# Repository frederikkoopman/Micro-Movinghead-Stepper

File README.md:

# Micro-Movinghead-Stepper
Micro Movinghead project stepper version

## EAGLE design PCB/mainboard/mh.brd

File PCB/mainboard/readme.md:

All Eagle files are here if your only interested in building not designing the zip file has all the files you need to order a PCB at your favorite PCB maker.

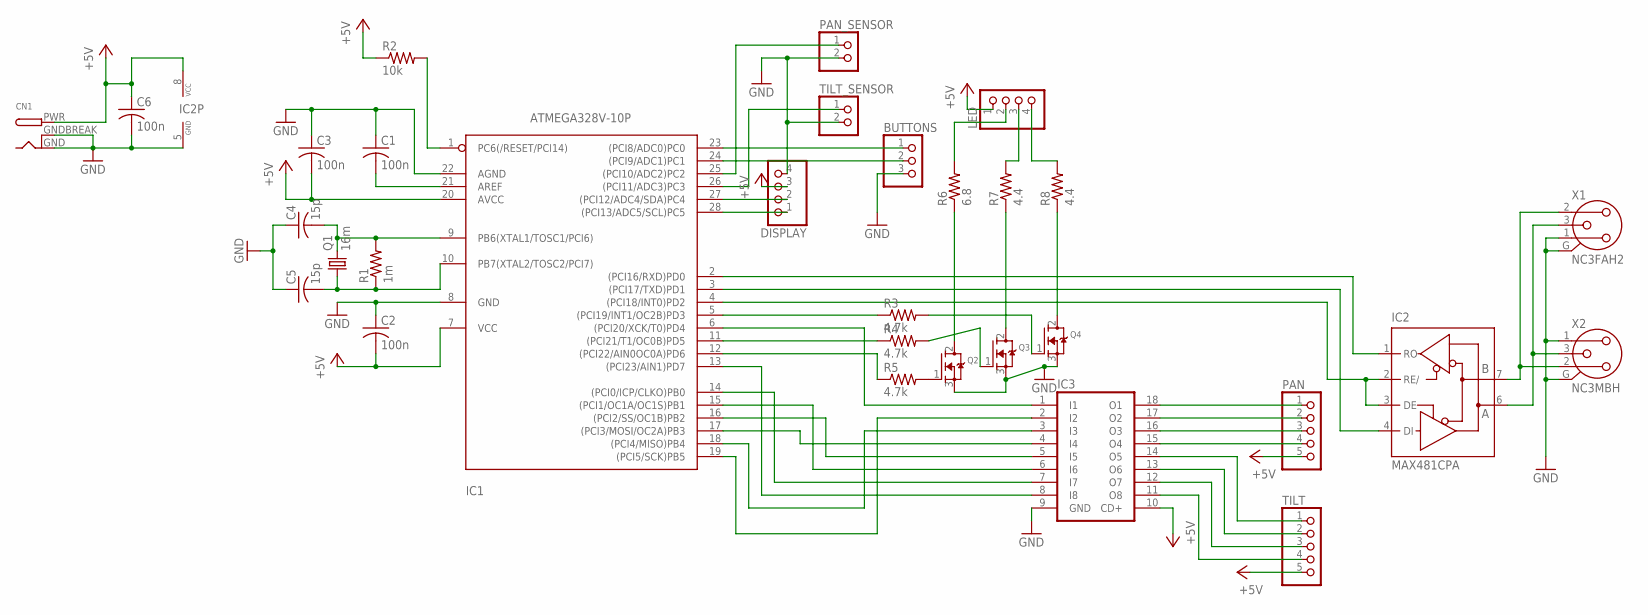
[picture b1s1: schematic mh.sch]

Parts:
BUTTONS: PINHD-1X3; 1X03
C1, C2, C3, C6: 100n; C025-024X044
C4, C5: 15p; C050-024X044
CN1: DCBARRELPTH; DCJACK_2MM_PTH
DISPLAY: PINHD-1X4; 1X04
IC1: ATMEGA328V-10P; DIL28-3
IC2: MAX481CPA; DIL08
IC3: ULN2803A; DIL18
LED: PINHD-1X4; 1X04
PAN: PINHD-1X5; 1X05
PAN_SENSOR: PINHD-1X2; 1X02
Q1: 16m; HC49/S
Q2, Q3, Q4: MOSFET-NGDS_TO220V; TO220V
R1: 1m; 0207/10
R2: 10k; 0207/10
R3, R4, R5: 4.7k; 0207/10
R6: 6.8; 0617/17
R7, R8: 4.4; 0617/17
TILT: PINHD-1X5; 1X05
TILT_SENSOR: PINHD-1X2; 1X02
X1: NC3FAH2
X2: NC3MBH

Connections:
+5V: C2.2, C3.2, C6.1, CN1.PWR, DISPLAY.3, IC1.7 (VCC), IC1.20 (AVCC), IC2.8 (VCC), IC3.10 (CD+), LED.1, PAN.5, R2.1, TILT.5
GND: BUTTONS.3, C1.1, C2.1, C3.1, C4.1, C5.1, C6.2, CN1.GND, CN1.GNDBREAK, DISPLAY.4, IC1.8 (GND), IC1.22 (AGND), IC2.5 (GND), IC3.9 (GND), PAN_SENSOR.2, Q2.3 (S), Q3.3 (S), Q4.3 (S), TILT_SENSOR.2, X1.1 (2), X1.G, X2.1, X2.G
unnamed: IC1.14 ((PCI0/ICP/CLKO)PB0), IC3.7 (I7)
unnamed: C5.2, IC1.10 (PB7(XTAL2/TOSC2/PCI7)), Q1.1, R1.1
unnamed: C1.2, IC1.21 (AREF)
unnamed: IC1.5 ((PCI19/INT1/OC2B)PD3), R3.1
unnamed: IC1.1 (PC6(/RESET/PCI14)), R2.2
unnamed: IC1.11 ((PCI21/T1/OC0B)PD5), R4.1
unnamed: IC1.12 ((PCI22/AIN0OC0A)PD6), R5.1
unnamed: Q2.1 (G), R5.2
unnamed: Q3.1 (G), R4.2
unnamed: Q4.1 (G), R3.2
unnamed: Q2.2 (D), R6.1
unnamed: Q3.2 (D), R7.1
unnamed: LED.4, R8.2
unnamed: LED.3, R7.2
unnamed: LED.2, R6.2
unnamed: IC1.19 ((PCI5/SCK)PB5), IC3.2 (I2)
unnamed: IC1.18 ((PCI4/MISO)PB4), IC3.3 (I3)
unnamed: IC1.17 ((PCI3/MOSI/OC2A)PB3), IC3.4 (I4)
unnamed: IC1.16 ((PCI2/SS/OC1B)PB2), IC3.5 (I5)
unnamed: IC1.15 ((PCI1/OC1A/OC1S)PB1), IC3.6 (I6)
unnamed: IC1.6 ((PCI20/XCK/T0)PD4), IC3.1 (I1)
unnamed: IC1.13 ((PCI23/AIN1)PD7), IC3.8 (I8)
unnamed: IC3.18 (O1), PAN.1
unnamed: IC3.17 (O2), PAN.2
unnamed: IC3.16 (O3), PAN.3
unnamed: IC3.15 (O4), PAN.4
unnamed: IC3.14 (O5), TILT.1
unnamed: IC3.13 (O6), TILT.2
unnamed: IC1.4 ((PCI18/INT0)PD2), IC2.2 (RE/), IC2.3 (DE)
unnamed: IC3.12 (O7), TILT.3
unnamed: IC1.3 ((PCI17/TXD)PD1), IC2.4 (DI)
unnamed: IC3.11 (O8), TILT.4
unnamed: DISPLAY.1, IC1.28 ((PCI13/ADC5/SCL)PC5)
unnamed: DISPLAY.2, IC1.27 ((PCI12/ADC4/SDA)PC4)
unnamed: IC1.2 ((PCI16/RXD)PD0), IC2.1 (RO)
unnamed: IC1.25 ((PCI10/ADC2)PC2), PAN_SENSOR.1
unnamed: IC1.26 ((PCI11/ADC3)PC3), TILT_SENSOR.1
unnamed: C4.2, IC1.9 (PB6(XTAL1/TOSC1/PCI6)), Q1.2, R1.2
unnamed: BUTTONS.1, IC1.23 ((PCI8/ADC0)PC0)
unnamed: IC2.7 (B), X1.2 (1), X2.2
unnamed: BUTTONS.2, IC1.24 ((PCI9/ADC1)PC1)
unnamed: IC2.6 (A), X1.3, X2.3
unnamed: Q4.2 (D), R8.1

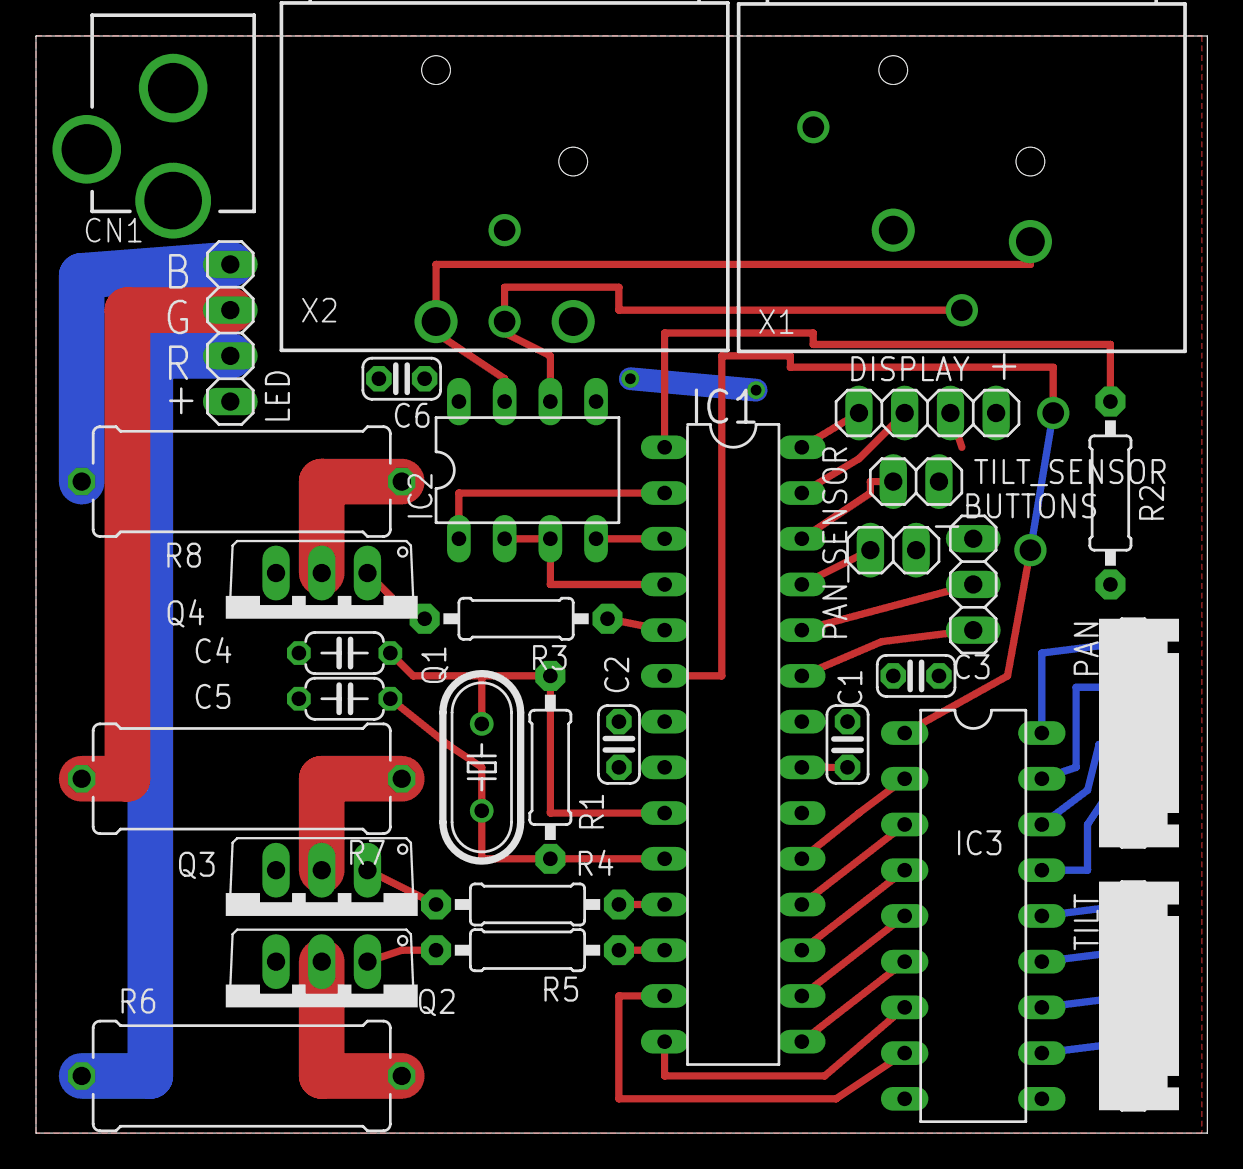
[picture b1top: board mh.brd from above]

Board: 2 copper layers, 65.1 x 61.0 mm, 31 parts (0 on the bottom side), 45 nets.

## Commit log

2017-03-17 Create bla
